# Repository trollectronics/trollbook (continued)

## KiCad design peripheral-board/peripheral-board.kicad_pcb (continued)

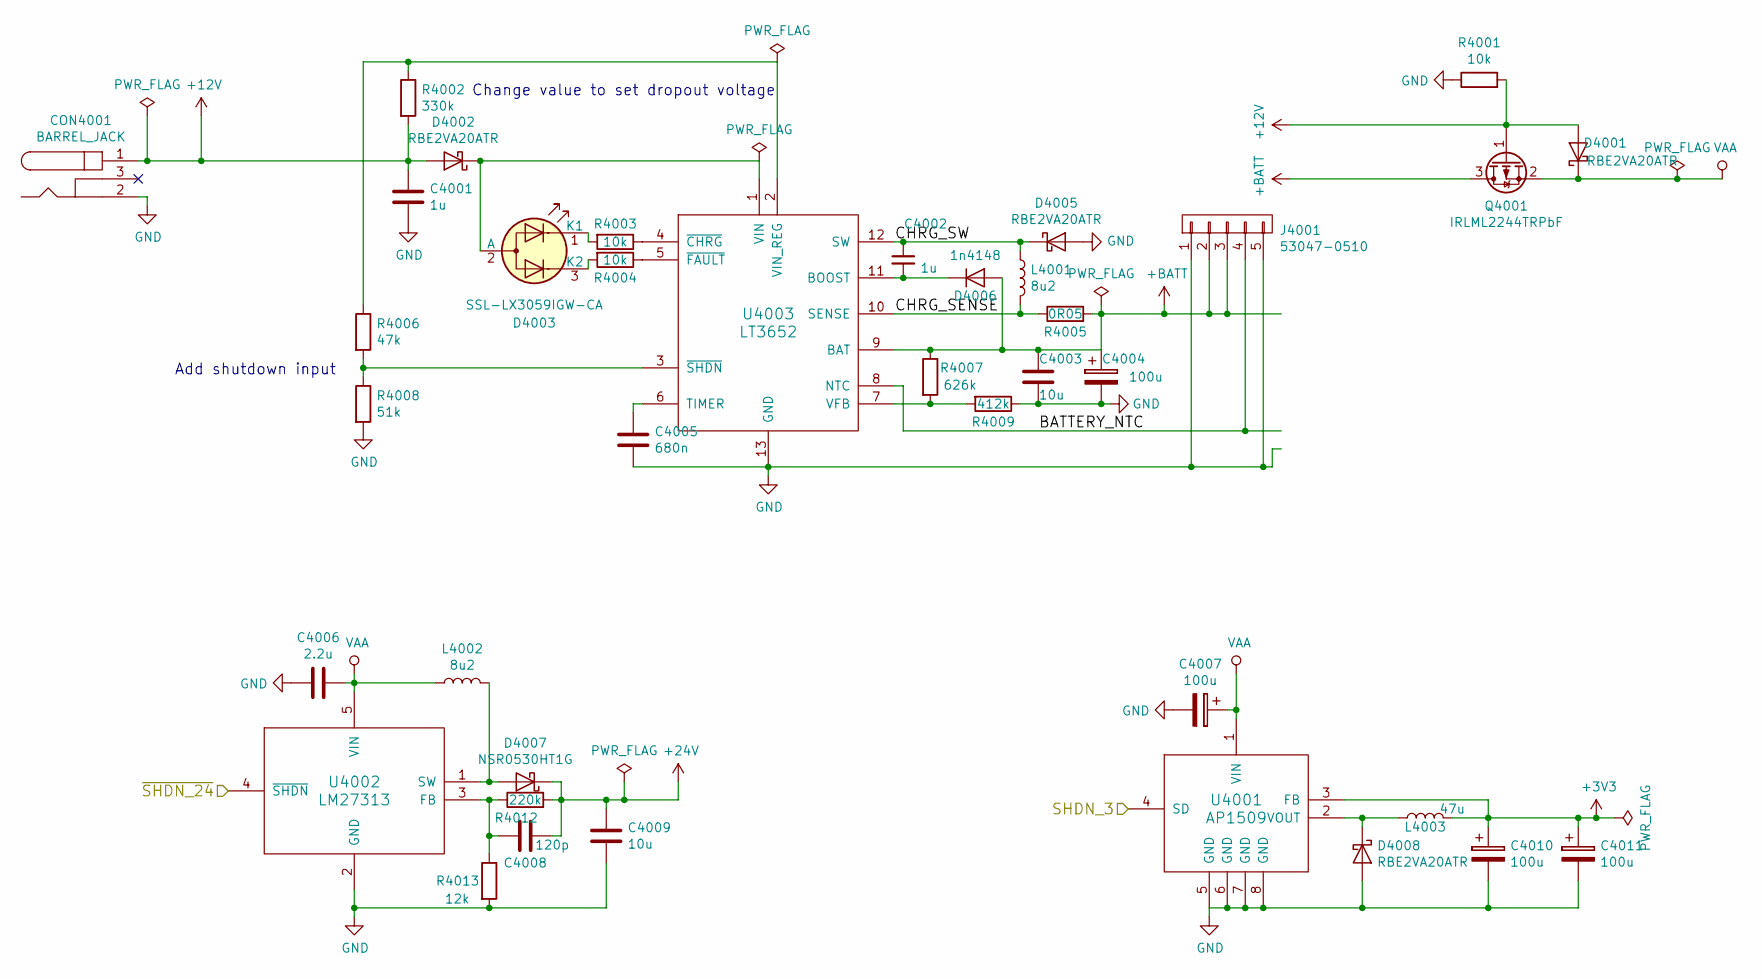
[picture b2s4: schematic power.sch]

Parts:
C4001, C4002: 1u; C_1206
C4003, C4009: 10u; C_1206
C4004, C4007: 100u; TantalC_SizeD_EIA-7343_Reflow
C4005: 680n; C_0805
C4006: 2.2u; C_1206
C4008: 120p; C_0805
C4010, C4011: 100u; c_elec_6.3x5.8
CON4001: BARREL_JACK; JACK_ALIM
D4001, D4002, D4005, D4008: RBE2VA20ATR; D_TUMD2
D4003: SSL-LX3059IGW-CA; LED-5MM-3
D4006: 1n4148; D_MiniMELF_Standard
D4007: NSR0530HT1G; D_SOD-323
J4001: 53047-0510; Connector_Molex_PicoBlade_53047-0510
L4001, L4002: 8u2; Choke_SMD_6.3x6.3_H3
L4003: 47u; Choke_SMD_12x12mm_h6mm
Q4001: IRLML2244TRPbF; SOT-23
R4001, R4003, R4004: 10k; R_0805
R4002: 330k; R_0805
R4005: 0R05; R_1812
R4006: 47k; R_0805
R4007: 626k; R_0805
R4008: 51k; R_0805
R4009: 412k; R_0805
R4012: 220k; R_0805
R4013: 12k; R_0805
U4001: AP1509; SOIC-8_3.9x4.9mm_Pitch1.27mm
U4002: LM27313; SOT-23-5
U4003: LT3652; MSOP-12-1EP_3x4mm_Pitch0.65mm

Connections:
+3V3: C4010.1, C4011.1, L4003.2, U4001.3 (FB); also elsewhere on the board
+12V: C4001.1, CON4001.1, D4001.2 (A), D4002.2 (A), Q4001.1 (G), R4001.2, R4002.2
+24V: C4008.1, C4009.1, D4007.1 (K), R4012.2; also elsewhere on the board
+BATT: C4003.1, C4004.1, D4006.2 (A), J4001.2, J4001.3, Q4001.3 (D), R4005.2, R4007.1, U4003.9 (BAT)
/PWR_SHDN_3: U4001.4 (SD); also elsewhere on the board
/PWR_SHDN_24: U4002.4 (~SHDN); also elsewhere on the board
/Power Supply/BATTERY_NTC: J4001.4, U4003.8 (NTC)
/Power Supply/CHRG_SENSE: L4001.2, R4005.1, U4003.10 (SENSE)
/Power Supply/CHRG_SW: C4002.1, D4005.1 (K), L4001.1, U4003.12 (SW)
GND: C4001.2, C4003.2, C4004.2, C4005.2, C4006.2, C4007.2, C4009.2, C4010.2, C4011.2, CON4001.2, D4005.2 (A), D4008.2 (A), J4001.1, J4001.5, R4001.1, R4008.2, R4009.1, R4013.2, U4001.5 (GND), U4001.6 (GND), U4001.7 (GND), U4001.8 (GND), U4002.2 (GND), U4003.13 (GND); also elsewhere on the board
unnamed: C4002.2, D4006.1 (K), U4003.11 (BOOST)
unnamed: C4005.1, U4003.6 (TIMER)
unnamed: C4008.2, R4012.1, R4013.1, U4002.3 (FB)
unnamed: D4002.1 (K), D4003.2 (A), U4003.1 (VIN)
unnamed: D4003.1 (K1), R4003.2
unnamed: D4003.3 (K2), R4004.2
unnamed: D4007.2 (A), L4002.2, U4002.1 (SW)
unnamed: D4008.1 (K), L4003.1, U4001.2 (VOUT)
unnamed: R4002.1, R4006.1, U4003.2 (VIN_REG)
unnamed: R4003.1, U4003.4 (~CHRG)
unnamed: R4004.1, U4003.5 (~FAULT)
unnamed: R4006.2, R4008.1, U4003.3 (~SHDN)
unnamed: R4007.2, R4009.2, U4003.7 (VFB)
VAA: C4006.1, C4007.1, D4001.1 (K), L4002.1, Q4001.2 (S), U4001.1 (VIN), U4002.5 (VIN); also elsewhere on the board

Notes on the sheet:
Change value to set dropout voltage
Add shutdown input

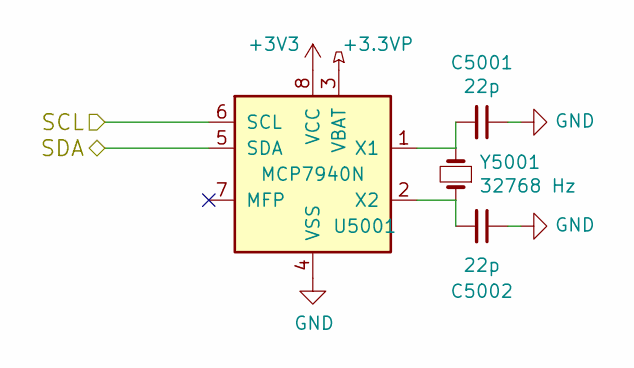
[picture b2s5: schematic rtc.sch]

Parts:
C5001, C5002: 22p; C_0603
U5001: MCP7940N; SOIC-8_3.9x4.9mm_Pitch1.27mm
Y5001: 32768 Hz; Crystal_Watch

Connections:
+3.3VP: U5001.3 (VBAT); also elsewhere on the board
+3V3: U5001.8 (VCC); also elsewhere on the board
/I2C_SCL: U5001.5 (SDA); also elsewhere on the board
/I2C_SDA: U5001.6 (SCL); also elsewhere on the board
GND: C5001.1, C5002.1, U5001.4 (VSS); also elsewhere on the board
unnamed: C5001.2, U5001.1 (X1), Y5001.2
unnamed: C5002.2, U5001.2 (X2), Y5001.1

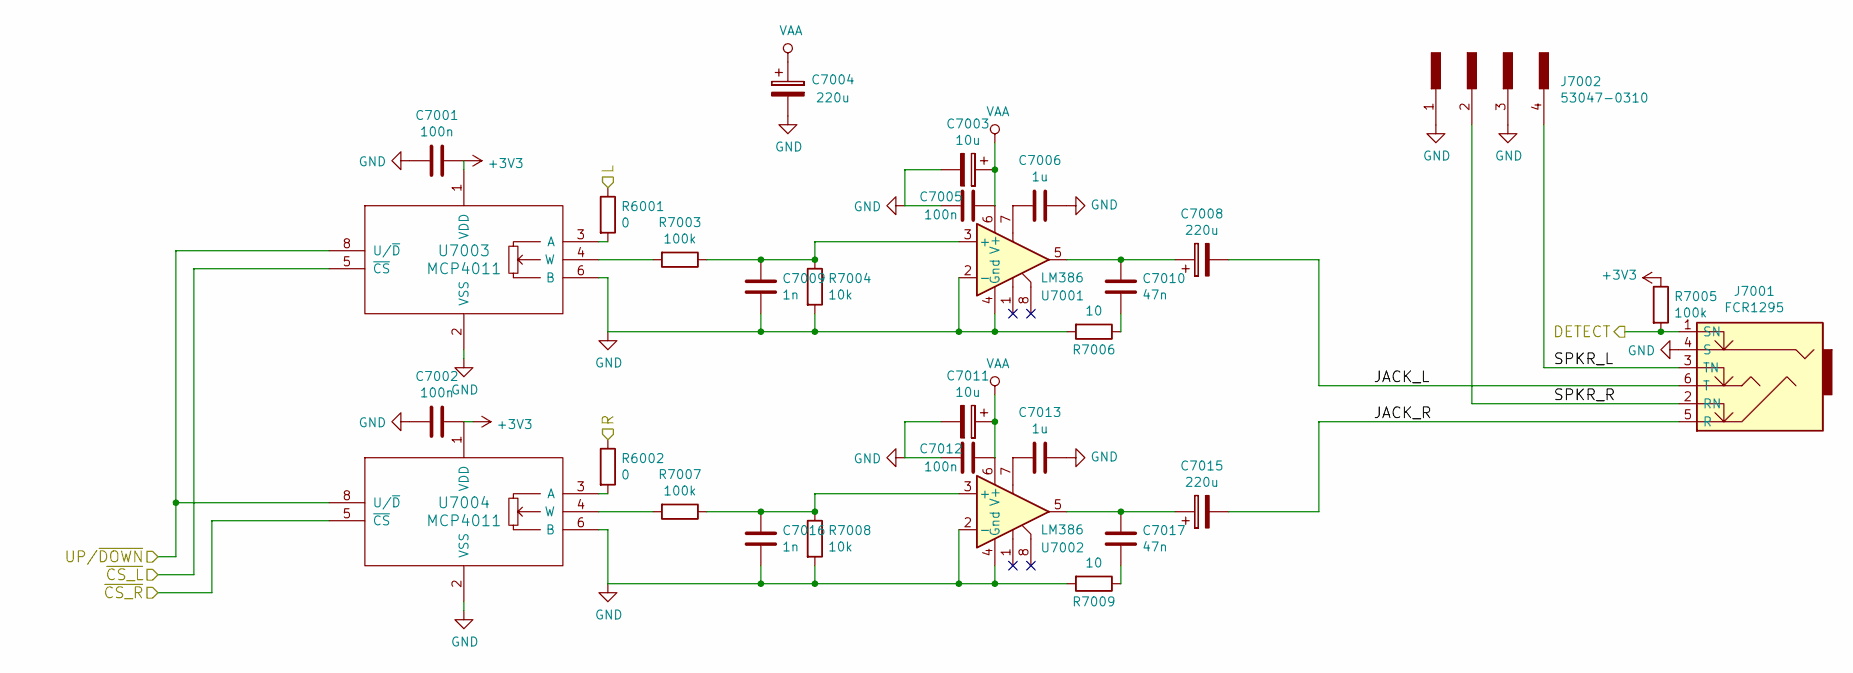
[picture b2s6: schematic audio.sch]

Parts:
C7001, C7002, C7005, C7012: 100n; C_0805
C7003, C7011: 10u; c_elec_6.3x5.8
C7004, C7008, C7015: 220u; c_elec_8x6.7
C7006, C7013: 1u; C_0805
C7009, C7016: 1n; C_0805
C7010, C7017: 47n; C_0805
J7001: FCR1295
J7002: 53047-0310; Connector_Molex_PicoBlade_53047-0410
R6001, R6002: 0; R_1206
R7003, R7005, R7007: 100k; R_0805
R7004, R7008: 10k; R_0805
R7006, R7009: 10; R_0805
U7001, U7002: LM386; SOIC-8_3.9x4.9mm_Pitch1.27mm
U7003, U7004: MCP4011; SOIC-8_3.9x4.9mm_Pitch1.27mm

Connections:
+3V3: C7001.1, C7002.1, R7005.1, U7003.1 (VDD), U7004.1 (VDD); also elsewhere on the board
/AUDIO_L: R6001.1; also elsewhere on the board
/AUDIO_R: R6002.1; also elsewhere on the board
/AUD_CS_L: U7003.5 (~CS); also elsewhere on the board
/AUD_CS_R: U7004.5 (~CS); also elsewhere on the board
/AUD_DET: J7001.1 (SN), R7005.2; also elsewhere on the board
/AUD_UD: U7003.8 (U/~D), U7004.8 (U/~D); also elsewhere on the board
/Audio/JACK_L: C7008.2, J7001.6 (T)
/Audio/JACK_R: C7015.2, J7001.5 (R)
/Audio/SPKR_L: J7001.3 (TN), J7002.4
/Audio/SPKR_R: J7001.2 (RN), J7002.2
GND: C7001.2, C7002.2, C7003.2, C7004.2, C7005.2, C7006.1, C7009.2, C7011.2, C7012.2, C7013.1, C7016.2, J7001.4 (S), J7002.1, J7002.3, R7004.2, R7006.2, R7008.2, R7009.2, U7001.2 (-), U7001.4 (Gnd), U7002.2 (-), U7002.4 (Gnd), U7003.2 (VSS), U7003.6 (B), U7004.2 (VSS), U7004.6 (B); also elsewhere on the board
unnamed: C7006.2, U7001.7
unnamed: C7008.1, C7010.1, U7001.5
unnamed: C7009.1, R7003.1, R7004.1, U7001.3 (+)
unnamed: C7010.2, R7006.1
unnamed: C7013.2, U7002.7
unnamed: C7015.1, C7017.1, U7002.5
unnamed: C7016.1, R7007.1, R7008.1, U7002.3 (+)
unnamed: C7017.2, R7009.1
unnamed: R6001.2, U7003.3 (A)
unnamed: R6002.2, U7004.3 (A)
unnamed: R7003.2, U7003.4 (W)
unnamed: R7007.2, U7004.4 (W)
VAA: C7003.1, C7004.1, C7005.1, C7011.1, C7012.1, U7001.6 (V+), U7002.6 (V+); also elsewhere on the board

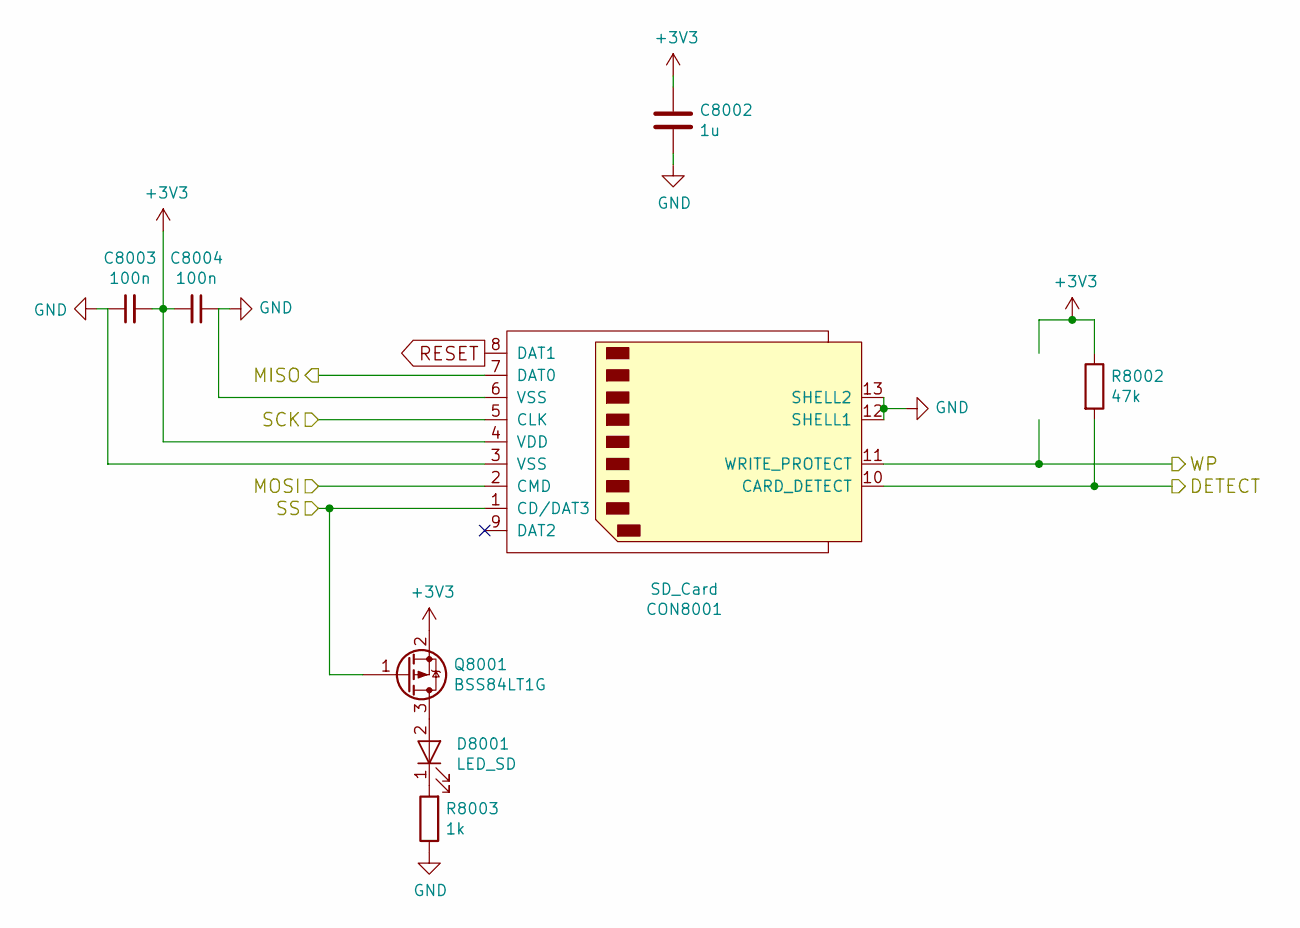
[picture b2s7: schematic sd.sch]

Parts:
C8002: 1u; C_0805
C8003, C8004: 100n; C_0805
CON8001: SD_Card; TS-2198-01
D8001: LED_SD; LED-3MM
Q8001: BSS84LT1G; SOT-23
R8002: 47k; R_0805
R8003: 1k; R_0805

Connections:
+3V3: C8002.1, C8003.2, C8004.2, CON8001.4 (VDD), Q8001.2 (S), R8002.1; also elsewhere on the board
/SD_DET: CON8001.10 (CARD_DETECT), R8002.2; also elsewhere on the board
/SD_WP: CON8001.11 (WRITE_PROTECT)
/SPI_MISO: CON8001.7 (DAT0); also elsewhere on the board
/SPI_MOSI: CON8001.2 (CMD); also elsewhere on the board
/SPI_SCK: CON8001.5 (CLK); also elsewhere on the board
/SPI_SS3: CON8001.1 (CD/DAT3), Q8001.1 (G); also elsewhere on the board
GND: C8002.2, C8003.1, C8004.1, CON8001.3 (VSS), CON8001.6 (VSS), CON8001.12 (SHELL1), CON8001.13 (SHELL2), R8003.1; also elsewhere on the board
unnamed: D8001.1 (K), R8003.2
unnamed: D8001.2 (A), Q8001.3 (D)
RESET: CON8001.8 (DAT1); also elsewhere on the board

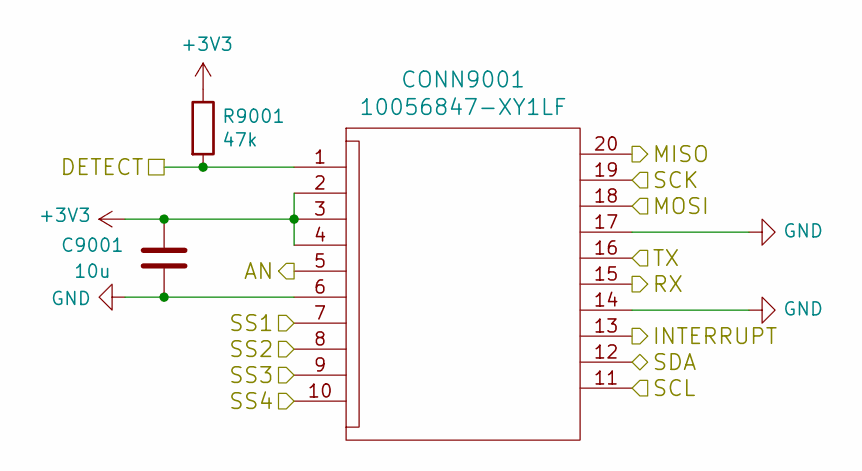
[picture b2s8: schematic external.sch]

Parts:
C9001: 10u; C_1206
CONN9001: 10056847-XY1LF
R9001: 47k; R_0805

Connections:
+3V3: C9001.1, CONN9001.2, CONN9001.3, CONN9001.4, R9001.1; also elsewhere on the board
/EXTINT1: CONN9001.13; also elsewhere on the board
/EXT_AN: CONN9001.5; also elsewhere on the board
/EXT_DET: CONN9001.1, R9001.2; also elsewhere on the board
/I2C_SCL: CONN9001.11; also elsewhere on the board
/I2C_SDA: CONN9001.12; also elsewhere on the board
/SPI_MISO: CONN9001.20; also elsewhere on the board
/SPI_MOSI: CONN9001.18; also elsewhere on the board
/SPI_SCK: CONN9001.19; also elsewhere on the board
/SPI_SS4: CONN9001.7; also elsewhere on the board
/SPI_SS5: CONN9001.8; also elsewhere on the board
/SPI_SS6: CONN9001.9; also elsewhere on the board
/SPI_SS7: CONN9001.10; also elsewhere on the board
/UART_RX: CONN9001.15; also elsewhere on the board
/UART_TX: CONN9001.16; also elsewhere on the board
GND: C9001.2, CONN9001.6, CONN9001.14, CONN9001.17; also elsewhere on the board

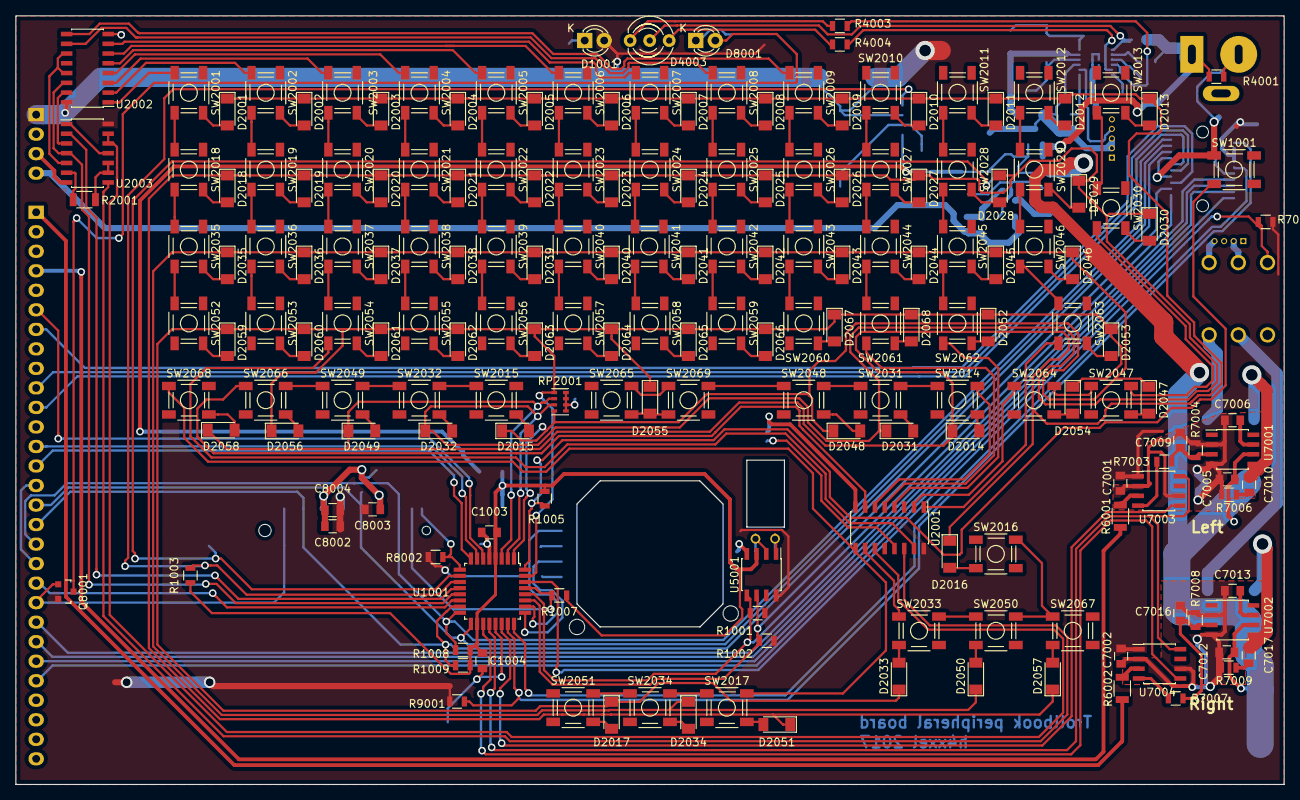
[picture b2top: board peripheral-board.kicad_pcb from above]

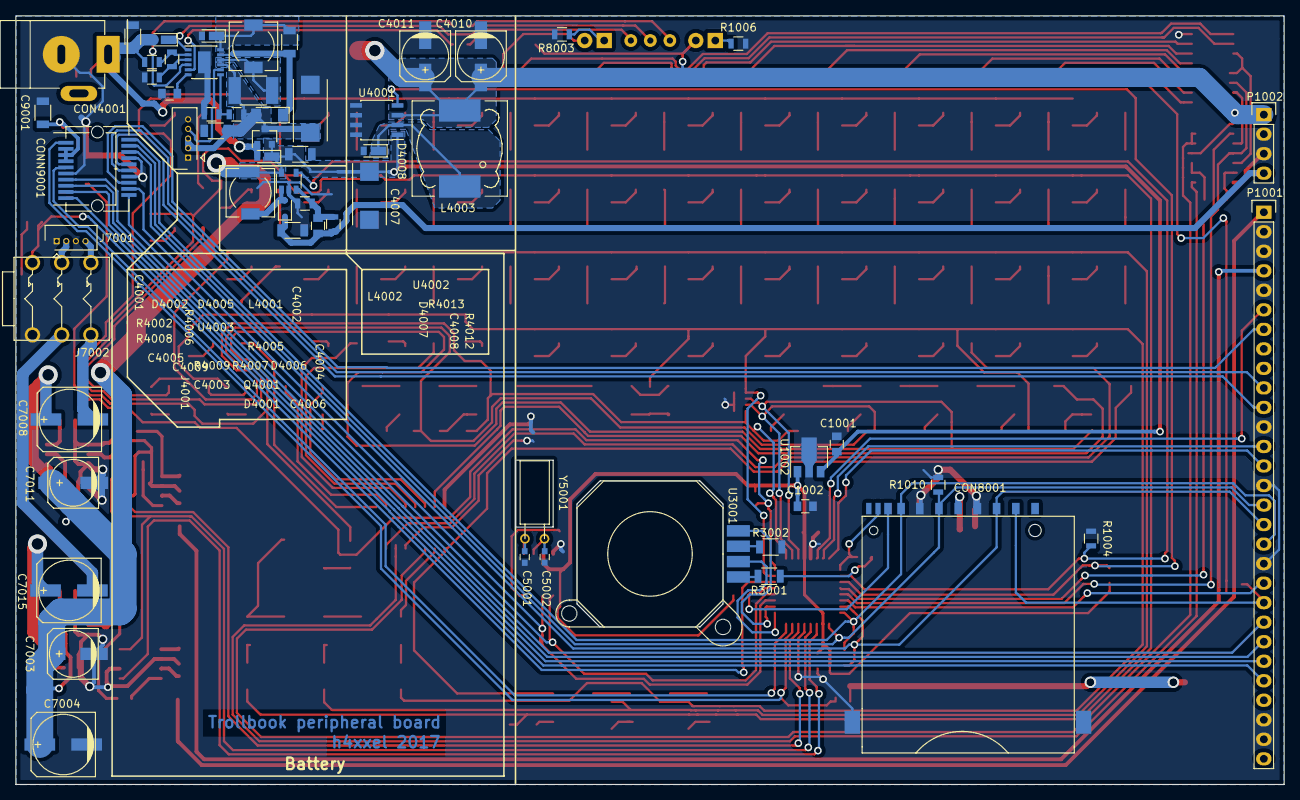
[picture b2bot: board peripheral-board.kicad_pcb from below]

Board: 2 copper layers, 165.0 x 100.0 mm, 248 parts (59 on the bottom side), 176 nets.

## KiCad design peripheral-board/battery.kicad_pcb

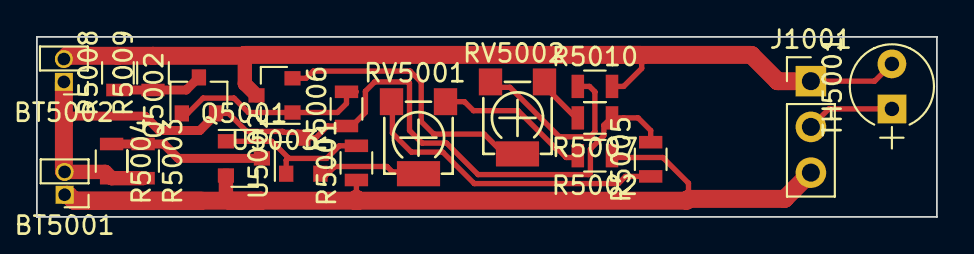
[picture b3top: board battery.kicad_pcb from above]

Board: 2 copper layers, 50.0 x 10.0 mm, 20 parts (0 on the bottom side), 14 nets.

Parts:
BT5001, BT5002: LiPo 2200mAh 51x68x5; Socket_Strip_Straight_1x02_Pitch1.27mm
J1001: CONN_01X03; Socket_Strip_Straight_1x03_Pitch2.54mm
Q5001, Q5002: IRLML2244TRPbF; SOT-23
R5001, R5006: 10k; R_0805
R5002, R5007: 150k; R_0805
R5003, R5004, R5008, R5009: 40R; R_0805
R5005, R5010: 220k; R_0805
RV5001, RV5002: 47k; 3364W
TH5001: 10k; CP_Radial_Tantal_D4.5mm_P2.50mm
U5002, U5003: TL431; SOT-23

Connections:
/B+: BT5001.1, J1001.3, Q5001.2, R5001.1, R5002.1
/B-: BT5002.2, J1001.1, R5008.2, R5009.2, R5010.2, TH5001.2, U5003.3
/NTC: J1001.2, TH5001.1
unnamed: BT5001.2, BT5002.1, Q5002.2, R5003.2, R5004.2, R5005.2, R5006.1, R5007.1, U5002.3
unnamed: Q5001.1, R5001.2, U5002.1
unnamed: Q5001.3, R5003.1, R5004.1
unnamed: Q5002.1, R5006.2, U5003.1
unnamed: Q5002.3, R5008.1, R5009.1
unnamed: R5002.2, RV5001.1
unnamed: R5005.1, RV5001.3
unnamed: R5007.2, RV5002.1
unnamed: R5010.1, RV5002.3
unnamed: RV5001.2, U5002.2
unnamed: RV5002.2, U5003.2

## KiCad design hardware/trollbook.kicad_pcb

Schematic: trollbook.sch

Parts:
C1, C2, C3, C4, C10, C12: 1n
C5, C6, C7, C8, C9, C11, C13, C14, C15, C16, C17, C18, C19, C20, C21, C22, C23, C24, C25, C26, C27, C28, C29, C30, C31, C32, C33, C41, C42, C43: 100n
C34, C35, C36, C37, C38, C39, C40: 10u
P1: VGA
P2: LCD_CONN
P3: SPI
P4: CONN_12
P5, P6, P7, P9, P11: CONN_2
P8: CONN_4
P10: CONN_1
R1, R2, R3, R10, R11, R12, R13: 10k
R4, R5, R6: 560k
R7, R8, R9: 150k
R17, R18, R19: 75
RP1, RP2, RP3, RP4: 20k
RP5, RP6, RP7, RP8: 10k
U1: XC95288-208
U2: MC68030
U3: MC68882
U4: IDT71V416
U5, U8: TLC7524
U6, U9, U10, U11: 74LVC574
U7: 39F040
U12, U13: HY57V561620
U15: 74HC4002
U16: ADA4851-4
U19: 74HC139
U20: 74LVC10
Y1: 50 MHz
Y2: 12.288 MHz

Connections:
3V3: C6.1, C8.1, C10.1, C12.1, C13.1, C14.1, C15.1, C16.1, C17.1, C22.1, C23.1, C24.1, C25.1, C26.1, C27.1, C34.1, C35.1, P2.7, P2.39, P4.1, R10.1, R11.1, R12.1, R13.1, U1.1 (VCCIO), U1.26 (VCCIO), U1.53 (VCCIO), U1.65 (VCCIO), U1.79 (VCCIO), U1.92 (VCCIO), U1.105 (VCCIO), U1.132 (VCCIO), U1.157 (VCCIO), U1.172 (VCCIO), U1.181 (VCCIO), U1.184 (VCCIO), U4.11 (VDD), U4.33 (VDD), U6.20 (VCC), U9.20 (VCC), U10.20 (VCC), U11.20 (VCC), U12.1 (Vdd), U12.3 (VddQ), U12.9 (VddQ), U12.14 (Vdd), U12.27 (Vdd), U12.37 (CKE), U12.43 (VddQ), U12.49 (VddQ), U13.1 (Vdd), U13.3 (VddQ), U13.9 (VddQ), U13.14 (Vdd), U13.27 (Vdd), U13.37 (CKE), U13.43 (VddQ), U13.49 (VddQ), U16.4 (VS+), U19.1 (E), U19.2 (A0), U19.3 (A1), U19.16 (VCC), U20.10, U20.11, U20.13, U20.14 (VCC), Y1.4 (VCC), Y2.4 (VCC)
+5V: C1.1, C2.1, C3.1, C4.1, C5.1, C7.1, C9.1, C11.1, C18.1, C19.1, C20.1, C21.1, C28.1, C29.1, C30.1, C31.1, C32.1, C33.1, C36.1, C37.1, P2.43, P4.3, U1.11 (VCC), U1.59 (VCC), U1.124 (VCC), U1.153 (VCC), U1.204 (VCC), U2.4 (VCC), U2.8 (VCC), U2.17 (~BGACK), U2.18 (VCC), U2.20 (~BR), U2.30 (VCC), U2.49 (VCC), U2.63 (VCC), U2.65 (~MMUDIS), U2.71 (~CDIS), U2.72 (VCC), U2.85 (VCC), U2.105 (VCC), U2.115 (VCC), U2.116 (VCC), U2.122 (~CIIN), U2.128 (VCC), U2.129 (~HALT), U3.10 (VCC), U3.16 (VCC), U3.17 (VCC), U3.18 (SIZE), U3.26 (A0), U3.27 (VCC), U3.43 (VCC), U3.52 (VCC), U3.53 (VCC), U3.61 (VCC), U5.1 (OUT1), U5.14 (VCC), U7.32 (VCC), U8.1 (OUT1), U8.14 (VCC), U15.9 (A), U15.10 (B), U15.11 (C), U15.12 (D), U15.14 (VCC)
+10V: C40.1, C43.1, P2.1, P2.2, P9.2 (PM)
+15V: C39.1, C42.1, P2.41, P4.7
-10V: C38.1, C41.1, P2.42, P4.9
/A0: U1.97 (IO71), U2.21 (A0), U7.12 (A0)
/A1: U1.95 (IO70), U2.22 (A1), U3.25 (A1), U7.11 (A1)
/A2: U1.38 (IO27), U2.59 (A2), U3.24 (A2), U7.10 (A2)
/A3: U1.39 (IO28), U2.58 (A3), U3.23 (A3), U7.9 (A3)
/A4: U1.40 (IO29), U2.56 (A4), U3.22 (A4), U7.8 (A4)
/A5: U1.41 (IO30), U2.55 (A5), U7.7 (A5)
/A6: U1.43 (IO31), U2.54 (A6), U7.6 (A6)
/A7: U1.45 (IO32), U2.53 (A7), U7.5 (A7)
/A8: U1.47 (IO33), U2.52 (A8), U7.27 (A8)
/A9: U1.48 (IO34), U2.51 (A9), U7.26 (A9)
/A10: U1.62 (IO44), U2.48 (A10), U7.23 (A10)
/A11: U1.63 (IO45), U2.47 (A11), U7.25 (A11)
/A12: U1.64 (IO46), U2.46 (A12), U7.4 (A12)
/A13: U1.66 (IO47), U2.45 (A13), U7.28 (A13)
/A14: U1.67 (IO48), U2.43 (A14), U7.29 (A14)
/A15: U1.69 (IO49), U2.42 (A15), U7.3 (A15)
/A16: U1.70 (IO50), U2.41 (A16), U7.2 (A16)
/A17: U1.71 (IO51), U2.40 (A17), U7.30 (A17)
/A18: U1.73 (IO53), U2.39 (A18), U7.1 (A18)
/A19: U1.74 (IO54), U2.38 (A19)
/A20: U1.75 (IO55), U2.37 (A20)
/A21: U1.76 (IO56), U2.36 (A21)
/A22: U1.78 (IO58), U2.34 (A22)
/A23: U1.80 (IO59), U2.33 (A23)
/A24: U1.82 (IO60), U2.32 (A24)
/A25: U1.83 (IO61), U2.31 (A25)
/A26: U1.86 (IO64), U2.29 (A26)
/A27: U1.87 (IO65), U2.28 (A27)
/A28: U2.27 (A28), U15.2 (A)
/A29: U2.26 (A29), U15.3 (B)
/A30: U2.24 (A30), U15.4 (C)
/A31: U2.23 (A31), U15.5 (D)
/AS: U1.140 (IO106), U2.125 (~AS), U3.21 (~AS)
/ATOOHIGH: U1.77 (IO57), U15.1 (Y)
/BERR: U1.134 (IO100), U2.130 (~BERR)
/CBACK: U1.138 (IO104), U2.127 (~CBACK)
/CBREQ: U1.139 (IO105), U2.126 (~CBREQ)
/CLK12: P7.1, U1.46 (GCK2), Y2.3 (CLKOUT)
/CLK50: U1.55 (GCK3), Y1.3 (CLKOUT)
/CPUCLK: U1.125 (IO94), U2.6 (CLK), U3.11 (CLOCK), U12.38 (CLK), U13.38 (CLK)
/CPUMODE: U1.101 (IO74), U20.6
/D0: U1.208 (IO160), U2.75 (D0), U3.3 (D0), U7.13 (D0)
/D1: U1.205 (IO159), U2.76 (D1), U3.2 (D1), U7.14 (D1)
/D2: U1.203 (IO158), U2.78 (D2), U3.1 (D2), U7.15 (D2)
/D3: U1.202 (IO157), U2.79 (D3), U3.68 (D3), U7.17 (D3)
/D4: U1.201 (IO156), U2.80 (D4), U3.67 (D4), U7.18 (D4)
/D5: U1.200 (IO155), U2.81 (D5), U3.66 (D5), U7.19 (D5)
/D6: U1.199 (IO154), U2.82 (D6), U3.65 (D6), U7.20 (D6)
/D7: U1.198 (IO153), U2.83 (D7), U3.64 (D7), U7.21 (D7)
/D8: U1.197 (IO152), U2.86 (D8), U3.62 (D8)
/D9: U1.196 (IO151), U2.87 (D9), U3.60 (D9)
/D10: U1.195 (IO150), U2.88 (D10), U3.59 (D10)
/D11: U1.194 (IO149), U2.89 (D11), U3.58 (D11)
/D12: U1.193 (IO148), U2.91 (D12), U3.57 (D12)
/D13: U1.192 (IO147), U2.92 (D13), U3.56 (D13)
/D14: U1.191 (IO146), U2.93 (D14), U3.55 (D14)
/D15: U1.189 (IO145), U2.94 (D15), U3.54 (D15)
/D16: U1.188 (IO144), U2.96 (D16), U3.50 (D16)
/D17: U1.187 (IO143), U2.97 (D17), U3.49 (D17)
/D18: U1.186 (IO142), U2.98 (D18), U3.48 (D18)
/D19: U1.185 (IO141), U2.99 (D19), U3.47 (D19)
/D20: U1.183 (IO140), U2.101 (D20), U3.46 (D20)
/D21: U1.182 (IO139), U2.102 (D21), U3.45 (D21)
/D22: U1.180 (IO138), U2.103 (D22), U3.44 (D22)
/D23: U1.179 (IO137), U2.104 (D23), U3.42 (D23)
/D24: U1.178 (IO136), U2.106 (D24), U3.40 (D24)
/D25: U1.175 (IO135), U2.107 (D25), U3.39 (D25)
/D26: U1.174 (IO134), U2.108 (D26), U3.38 (D26)
/D27: U1.173 (IO133), U2.109 (D27), U3.37 (D27)
/D28: U1.171 (IO132), U2.111 (D28), U3.36 (D28)
/D29: U1.170 (IO131), U2.112 (D29), U3.35 (D29)
/D30: U1.169 (IO130), U2.113 (D30), U3.34 (D30)
/D31: U1.168 (IO129), U2.114 (D31), U3.33 (D31)
/DS: U1.142 (IO107), U2.124 (~DS), U3.20 (~DS)
/DSACK0: U1.128 (IO97), U2.3 (~DSACK0), U3.32 (~DSACK1)
/DSACK1: U1.131 (IO98), U2.132 (~DSACK1), U3.31 (~DSACK0)
/EXTINT: P11.1, U1.44 (GCK1)
/FC0: U2.12 (FC0), U20.3
/FC1: U2.10 (FC1), U20.4
/FC2: U2.9 (FC2), U20.5
/FPUCS: U1.160 (IO122), U3.29 (~CS)
/IPL0: U1.167 (IO128), U2.70 (~IPL0)
/IPL1: U1.126 (IO95), U2.69 (~IPL1)
/IPL2: U1.91 (IO69), U2.68 (~IPL2)
/LLA1: U1.29 (IO18), U4.1 (A1)
/LLA2: U1.28 (IO17), U4.2 (A2)
/LLA3: U1.25 (IO16), U4.3 (A3)
/LLA4: U1.23 (IO15), U4.4 (A4)
/LLA5: U1.22 (IO14), U4.5 (A5)
/LLA6: U1.17 (IO9), U4.18 (A6)
/LLA7: U1.18 (IO10), U4.19 (A7)
/LLA8: U1.19 (IO11), U4.20 (A8)
/LLA9: U1.20 (IO12), U4.21 (A9)
/LLA10: U1.21 (IO13), U4.22 (A10)
/LLA11: U1.50 (IO36), U4.23 (A11)
/LLA12: U1.49 (IO35), U4.24 (A12)
/LLA13: U1.51 (IO37), U4.25 (A13)
/LLA14: U1.54 (IO38), U4.26 (A14)
/LLA15: U1.56 (IO39), U4.27 (A15)
/LLA16: U1.57 (IO40), U4.42 (A16)
/LLA17: U1.58 (IO41), U4.43 (A17)
/LLA18: U1.60 (IO42), U4.44 (A18)
/LLBHE: U1.5 (GTS4), U4.40 (~BHE)
/LLBLE: U1.7 (GTS1), U4.39 (~BLE)
/LLD0: U1.4 (IO1), U4.7 (D0), U6.2 (D0), U9.9 (D7)
/LLD1: U1.6 (IO2), U4.8 (D1), U6.3 (D1), U9.8 (D6)
/LLD2: U1.8 (IO3), U4.9 (D2), U6.4 (D2), U9.7 (D5)
/LLD3: U1.10 (IO4), U4.10 (D3), U6.5 (D3), U9.6 (D4)
/LLD4: U1.12 (IO5), U4.13 (D4), U6.6 (D4), U9.5 (D3)
/LLD5: U1.14 (IO6), U4.14 (D5), U6.7 (D5), U9.4 (D2)
/LLD6: U1.16 (IO8), U4.15 (D6), U6.8 (D6), U9.3 (D1)
/LLD7: U1.15 (IO7), U4.16 (D7), U6.9 (D7), U9.2 (D0)
/LLD8: U1.37 (IO26), U4.29 (D8), U10.9 (D7), U11.2 (D0)
/LLD9: U1.36 (IO25), U4.30 (D9), U10.8 (D6), U11.3 (D1)
/LLD10: U1.35 (IO24), U4.31 (D10), U10.7 (D5), U11.4 (D2)
/LLD11: U1.34 (IO23), U4.32 (D11), U10.6 (D4), U11.5 (D3)
/LLD12: U1.33 (IO22), U4.35 (D12), U10.5 (D3), U11.6 (D4)
/LLD13: U1.32 (IO21), U4.36 (D13), U10.4 (D2), U11.7 (D5)
/LLD14: U1.31 (IO20), U4.37 (D14), U10.3 (D1), U11.8 (D6)
/LLD15: U1.30 (IO19), U4.38 (D15), U10.2 (D0), U11.9 (D7)
/LLOE: U1.3 (GTS3), U4.41 (~OE)
/LLWEN: U1.9 (GTS2), U4.17 (~WEN)
/RAMA0: U1.118 (IO88), U12.23 (A0), U13.23 (A0)
/RAMA1: U1.117 (IO87), U12.24 (A1), U13.24 (A1)
/RAMA2: U1.116 (IO86), U12.25 (A2), U13.25 (A2)
/RAMA3: U1.115 (IO85), U12.26 (A3), U13.26 (A3)
/RAMA4: U1.114 (IO84), U12.29 (A4), U13.29 (A4)
/RAMA5: U1.113 (IO83), U12.30 (A5), U13.30 (A5)
/RAMA6: U1.112 (IO82), U12.31 (A6), U13.31 (A6)
/RAMA7: U1.111 (IO81), U12.32 (A7), U13.32 (A7)
/RAMA8: U1.109 (IO79), U12.33 (A8), U13.33 (A8)
/RAMA9: U1.107 (IO78), U12.34 (A9), U13.34 (A9)
/RAMA10: U1.119 (IO89), U12.22 (A10/AP), U13.22 (A10/AP)
/RAMA11: U1.106 (IO77), U12.35 (A11), U13.35 (A11)
/RAMA12: U1.102 (IO75), U12.36 (A12), U13.36 (A12)
/RAMB0: U1.135 (IO101), U12.20 (BA0), U13.20 (BA0)
/RAMB1: U1.127 (IO96), U12.21 (BA1), U13.21 (BA1)
/RAMCAS: U1.121 (IO91), U12.17 (~CAS), U13.17 (~CAS)
/RAMCS0: U1.110 (IO80), U12.19 (~CS), U20.9
/RAMCS1: U13.19 (~CS), U20.8
/RAMD0: U1.159 (IO121), U12.2 (D0), U13.2 (D0)
/RAMD1: U1.158 (IO120), U12.4 (D1), U13.4 (D1)
/RAMD2: U1.155 (IO119), U12.5 (D2), U13.5 (D2)
/RAMD3: U1.154 (IO118), U12.7 (D3), U13.7 (D3)
/RAMD4: U1.152 (IO117), U12.8 (D4), U13.8 (D4)
/RAMD5: U1.151 (IO116), U12.10 (D5), U13.10 (D5)
/RAMD6: U1.150 (IO115), U12.11 (D6), U13.11 (D6)
/RAMD7: U1.149 (IO114), U12.13 (D7), U13.13 (D7)
/RAMD8: U1.148 (IO113), U12.42 (D8), U13.42 (D8)
/RAMD9: U1.147 (IO112), U12.44 (D9), U13.44 (D9)
/RAMD10: U1.146 (IO111), U12.45 (D10), U13.45 (D10)
/RAMD11: U1.145 (IO110), U12.47 (D11), U13.47 (D11)
/RAMD12: U1.144 (IO109), U12.48 (D12), U13.48 (D12)
/RAMD13: U1.143 (IO108), U12.50 (D13), U13.50 (D13)
/RAMD14: U1.137 (IO103), U12.51 (D14), U13.51 (D14)
/RAMD15: U1.136 (IO102), U12.53 (D15), U13.53 (D15)
/RAMLDQM: U1.123 (IO93), U12.15 (LDQM), U13.15 (LDQM)
/RAMRAS: U1.120 (IO90), U12.18 (~RAS), U13.18 (~RAS)
/RAMUDQM: U1.103 (IO76), U12.39 (UDQM), U13.39 (UDQM)
/RAMWE: U1.122 (IO92), U12.16 (~WE), U13.16 (~WE)
/ROMCE: U1.161 (IO123), U7.22 (~CE)
/ROMOE: U1.162 (IO124), U7.24 (~OE)
/RW: U1.164 (IO125), U2.117 (R/~W), U3.28 (R/~W), U7.31 (~WE)
/SIZ0: U1.166 (IO127), U2.120 (SIZ0)
/SIZ1: U1.165 (IO126), U2.119 (SIZ1)
/SNDLATCH: U1.72 (IO52), U6.11 (Cp), U11.11 (Cp)
/SPICLK: P3.1, U1.88 (IO66)
/SPIMISO: P3.2, U1.89 (IO67)
/SPIMOSI: P3.3, U1.90 (IO68)
/SPISS1: P3.4, U19.12 (O0)
/SPISS2: P3.5, U19.11 (O1)
/SPISS3: P3.6, U19.10 (O2)
/SPISS4: P3.7, U19.9 (O3)
/SSBIN0: U1.99 (IO72), U19.14 (A0)
/SSBIN1: U1.100 (IO73), U19.13 (A1)
/STERM: U1.133 (IO99), U2.131 (STERM)
/VCOM: P2.6, P2.46, P4.11
/VGAB0: P2.16, RP2.8 (R1), U9.12 (Q7)
/VGAB1: P2.15, RP1.5 (R4), U9.13 (Q6)
/VGAB2: P2.14, RP1.6 (R3), U9.14 (Q5)
/VGAB3: P2.13, RP1.7 (R2), U9.15 (Q4)
/VGAB4: P2.12, RP1.8 (R1), U9.16 (Q3)
/VGAG0: P2.25, RP3.6 (R3), U9.17 (Q2)
/VGAG1: P2.24, RP3.7 (R2), U9.18 (Q1)
/VGAG2: P2.23, RP3.8 (R1), U9.19 (Q0)
/VGAG3: P2.22, RP2.5 (R4), U10.12 (Q7)
/VGAG4: P2.21, RP2.6 (R3), U10.13 (Q6)
/VGAG5: P2.20, RP2.7 (R2), U10.14 (Q5)
/VGAHSYNC: P1.4, P2.11, U1.85 (IO63), U20.1
/VGALATCH: P2.37, U1.61 (IO43), U9.11 (Cp), U10.11 (Cp)
/VGAOE: U9.1 (OE), U10.1 (OE), U20.12
/VGAR0: P2.32, RP4.5 (R4), U10.15 (Q4)
/VGAR1: P2.31, RP4.6 (R3), U10.16 (Q3)
/VGAR2: P2.30, RP4.7 (R2), U10.17 (Q2)
/VGAR3: P2.29, RP4.8 (R1), U10.18 (Q1)
/VGAR4: P2.28, RP3.5 (R4), U10.19 (Q0)
/VGAVSYNC: P1.5, P2.10, U1.84 (IO62), U20.2
unnamed: R5.2, RP2.2, RP6.7 (R2)
unnamed: R6.2, RP3.4, RP7.5 (R4)
unnamed: RP4.1, RP7.4, RP8.8 (R1)
unnamed: RP2.3, RP6.2, RP6.6 (R3)
unnamed: RP2.4, RP6.3, RP6.5 (R4)
unnamed: RP3.1, RP6.4, RP7.8 (R1)
unnamed: RP3.2, RP7.1, RP7.7 (R2)
unnamed: RP3.3, RP7.2, RP7.6 (R3)
unnamed: RP1.2, RP5.1, RP5.7 (R2)
unnamed: RP1.4, RP5.3, RP5.5 (R4)
unnamed: RP4.4, RP8.3, RP8.5 (R4)
unnamed: RP4.2, RP8.1, RP8.7 (R2)
unnamed: P1.3, R19.2
unnamed: P1.1, R17.2
unnamed: RP4.3, RP8.2, RP8.6 (R3)
unnamed: RP2.1, RP5.4, RP6.8 (R1)
unnamed: R1.1, RP6.1
unnamed: R2.1, RP7.3
unnamed: R3.1, RP8.4
unnamed: RP1.3, RP5.2, RP5.6 (R3)
unnamed: U8.7 (D4), U11.15 (Q4)
unnamed: U8.8 (D3), U11.16 (Q3)
unnamed: U8.9 (D2), U11.17 (Q2)
unnamed: U8.10 (D1), U11.18 (Q1)
unnamed: U8.11 (D0), U11.19 (Q0)
unnamed: P6.2 (PM), U8.15 (REF)
unnamed: U8.6 (D5), U11.14 (Q5)
unnamed: U5.10 (D1), U6.18 (Q1)
unnamed: U5.4 (D7), U6.12 (Q7)
unnamed: U5.5 (D6), U6.13 (Q6)
unnamed: U5.7 (D4), U6.15 (Q4)
unnamed: U5.8 (D3), U6.16 (Q3)
unnamed: U5.9 (D2), U6.17 (Q2)
unnamed: U5.11 (D0), U6.19 (Q0)
unnamed: P5.2 (PM), U5.15 (REF)
unnamed: U8.5 (D6), U11.13 (Q6)
unnamed: R5.1, R9.2, U16.5 (IN+)
unnamed: R4.1, RP1.1, RP5.8 (R1)
unnamed: P2.44, P10.1
unnamed: P8.4, R10.2, U1.98 (TCK)
unnamed: P8.3, R11.2, U1.94 (TDI)
unnamed: P8.2, R12.2, U1.96 (TMS)
unnamed: P8.1, R13.2, U1.176 (TDO)
unnamed: R6.1, R8.2, U16.10 (IN+)
unnamed: R17.1, U16.1 (OUT), U16.2 (IN-)
unnamed: P1.2, R18.2
unnamed: R4.2, R7.2, U16.3 (IN+)
unnamed: U8.4 (D7), U11.12 (Q7)
unnamed: U5.6 (D5), U6.14 (Q5)
unnamed: R18.1, U16.6 (IN-), U16.7 (OUT)
unnamed: R19.1, U16.8 (OUT), U16.9 (IN-)

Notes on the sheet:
spi slave select
Retarded datasheet does not specify polarity

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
